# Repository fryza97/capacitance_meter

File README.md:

# capacitance_meter
A laboratory circuit for C measurements based on a direct sensor-to-microcontroller interface circuit and a PIC16F1789 microcontroller.
Engineering thesis from 2020.

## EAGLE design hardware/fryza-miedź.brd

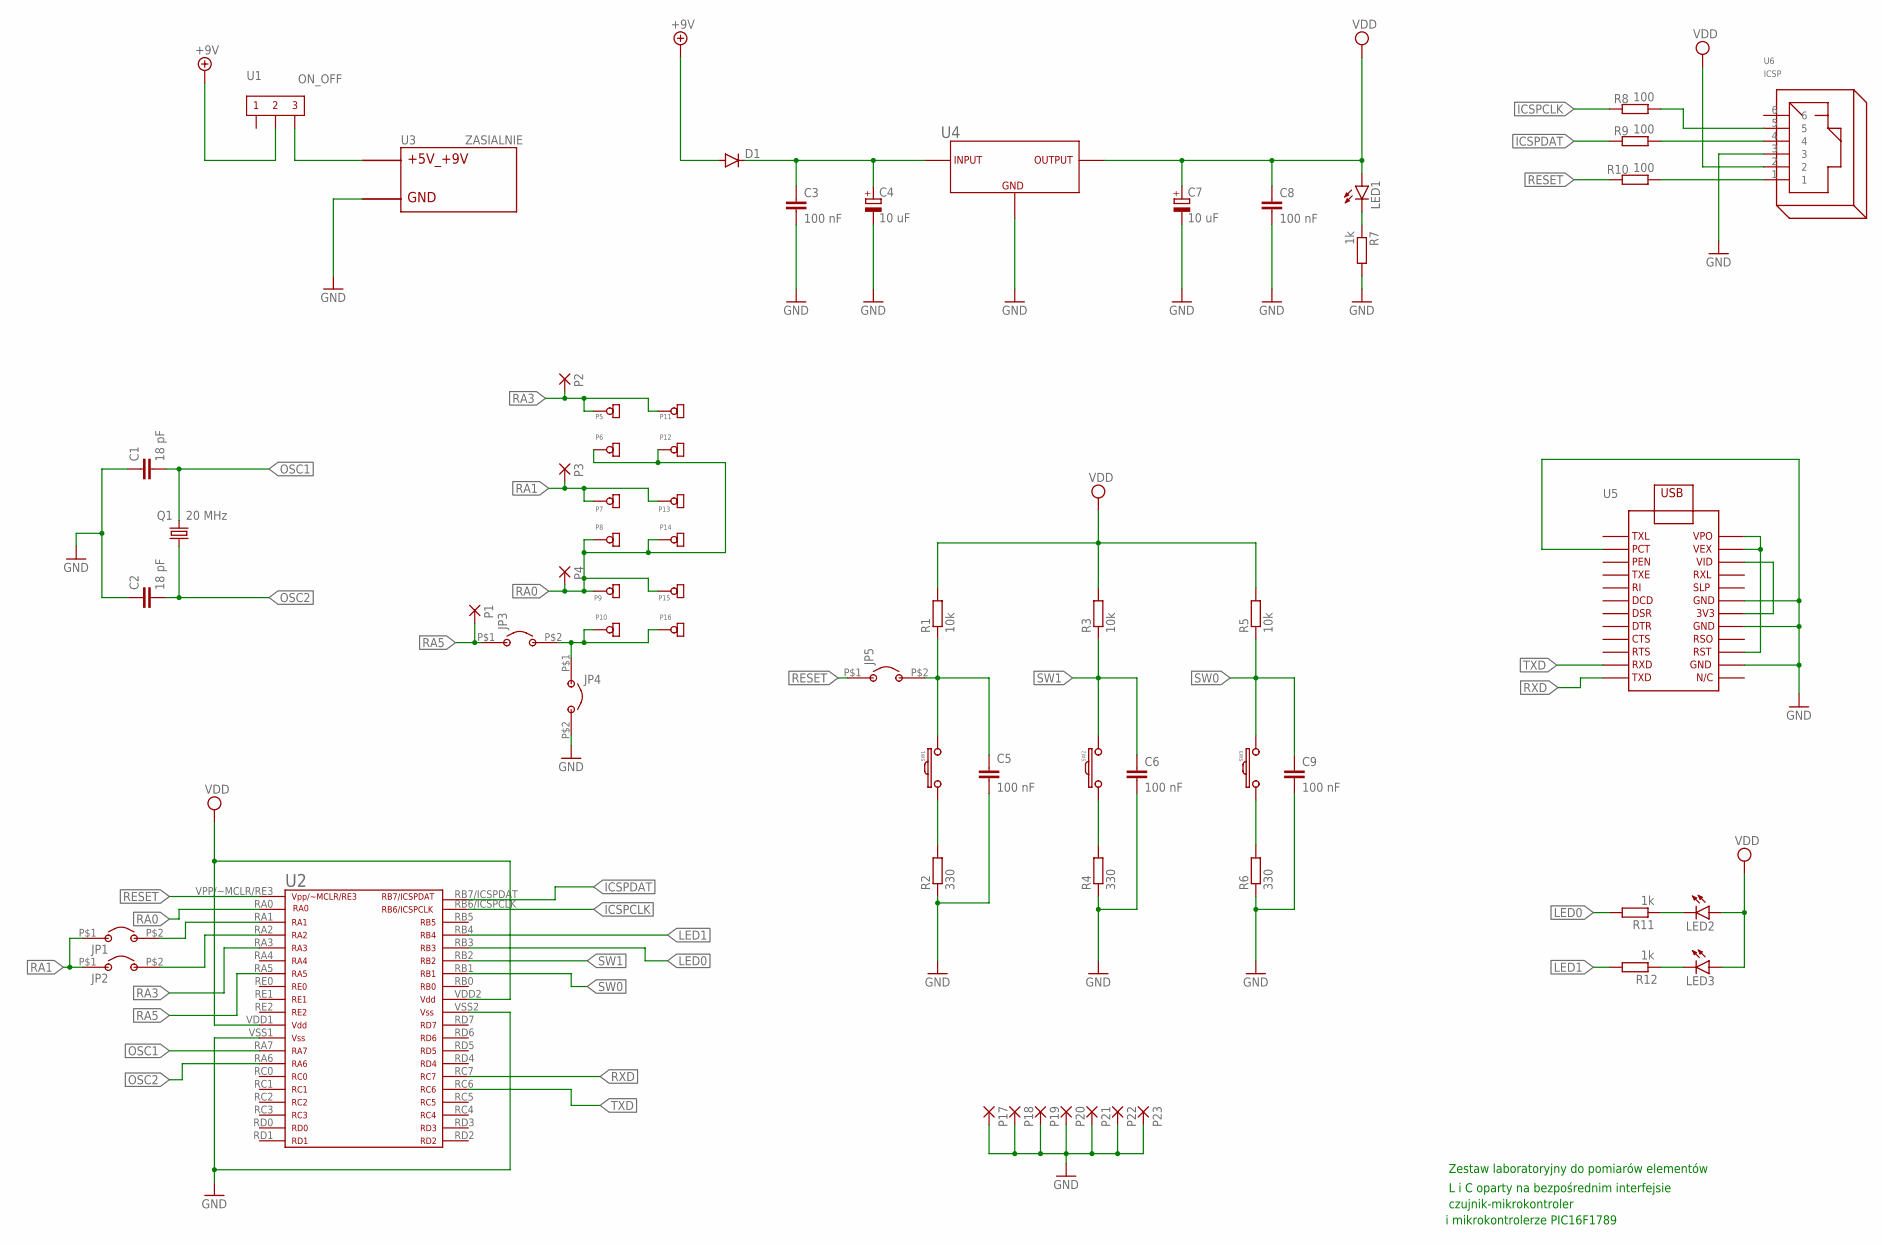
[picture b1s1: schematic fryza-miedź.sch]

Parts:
C1, C2: 18 pF; C050-035X075
C3, C5, C6, C8, C9: 100 nF; C050-035X075
C4, C7: 10 uF; E2,5-5
D1: 1N4004; DO41-10
JP1, JP2, JP3, JP4, JP5: JUMPER
LED1, LED2, LED3: LED5MM
P1, P2, P3, P4, P17, P18, P19, P20, P21, P22, P23: SZPILKA; CON
P5, P6, P7, P8, P9, P10, P11, P12, P13, P14, P15, P16: CON
Q1: 20 MHz; KWARC
R1, R3, R5: 10k; 0207/10
R2, R4, R6: 330; 0207/10
R7, R11, R12: 1k; 0207/10
R8, R9, R10: 100; 0207/10
SW1, SW2, SW3: PUSH_SWITCH
U1: ON_OFF; WLACZNIK
U2: PIC16F1789
U3: ZASIALNIE; ZASILANIE_ZLACZE
U4: LF33CV
U5: MMUSB232
U6: ICSP; RJ12

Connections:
+9V: D1.A, U1.2
GND: C1.1, C2.1, C3.2, C4.-, C5.2, C6.2, C7.-, C8.2, C9.2, JP4.P$2, P17.P$1, P18.P$1, P19.P$1, P20.P$1, P21.P$1, P22.P$1, P23.P$1, R2.1, R4.1, R6.1, R7.2, U2.VSS1, U2.VSS2, U3.GND1 (GND), U3.GND2 (GND), U4.GND, U5.GND, U5.GND1, U5.GND2, U5.PCT, U6.3
ICSPCLK: R8.2, U2.RB6/ICSPCLK
ICSPDAT: R9.2, U2.RB7/ICSPDAT
LED0: R11.2, U2.RB3
LED1: R12.2, U2.RB4
unnamed: C3.1, C4.+, D1.C, U4.INPUT
unnamed: LED1.K (C), R7.1
unnamed: U1.3, U3.V_S (+5V_+9V)
unnamed: C5.1, JP5.P$2, R1.1, SW1.1_1, SW1.1_2
unnamed: U5.RST, U5.VEX, U5.VPO
unnamed: JP3.P$2, JP4.P$1, P10.P$1, P16.P$1
unnamed: LED2.K (C), R11.1
unnamed: JP1.P$2, U2.RA1
unnamed: LED3.K (C), R12.1
unnamed: R10.1, U6.1
unnamed: R2.2, SW1.2_1, SW1.2_2
unnamed: R6.2, SW3.2_1, SW3.2_2
unnamed: R4.2, SW2.2_1, SW2.2_2
unnamed: U5.3V3, U5.VIO (VID)
unnamed: R8.1, U6.5
unnamed: R9.1, U6.4
OSC1: C1.2, Q1.P$2 (2), U2.RA7
OSC2: C2.2, Q1.P$1 (1), U2.RA6
RA0: P4.P$1, P6.P$1, P8.P$1, P9.P$1, P12.P$1, P14.P$1, P15.P$1, U2.RA0
RA1: JP1.P$1, JP2.P$1, P3.P$1, P7.P$1, P13.P$1
RA2: JP2.P$2, U2.RA2
RA3: P2.P$1, P5.P$1, P11.P$1, U2.RA3
RA5: JP3.P$1, P1.P$1, U2.RA5
RESET: JP5.P$1, R10.2, U2.VPP/~MCLR/RE3
RXD: U2.RC7, U5.TXD
SW0: C9.1, R5.1, SW3.1_1, SW3.1_2, U2.RB1
SW1: C6.1, R3.1, SW2.1_1, SW2.1_2, U2.RB2
TXD: U2.RC6, U5.RXD
VDD: C7.+, C8.1, LED1.A, LED2.A, LED3.A, R1.2, R3.2, R5.2, U2.VDD1, U2.VDD2, U4.OUTPUT, U6.2

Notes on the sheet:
Zestaw laboratoryjny do pomiarów elementów
L i C oparty na bezpośrednim interfejsie
czujnik-mikrokontroler
i mikrokontrolerze PIC16F1789

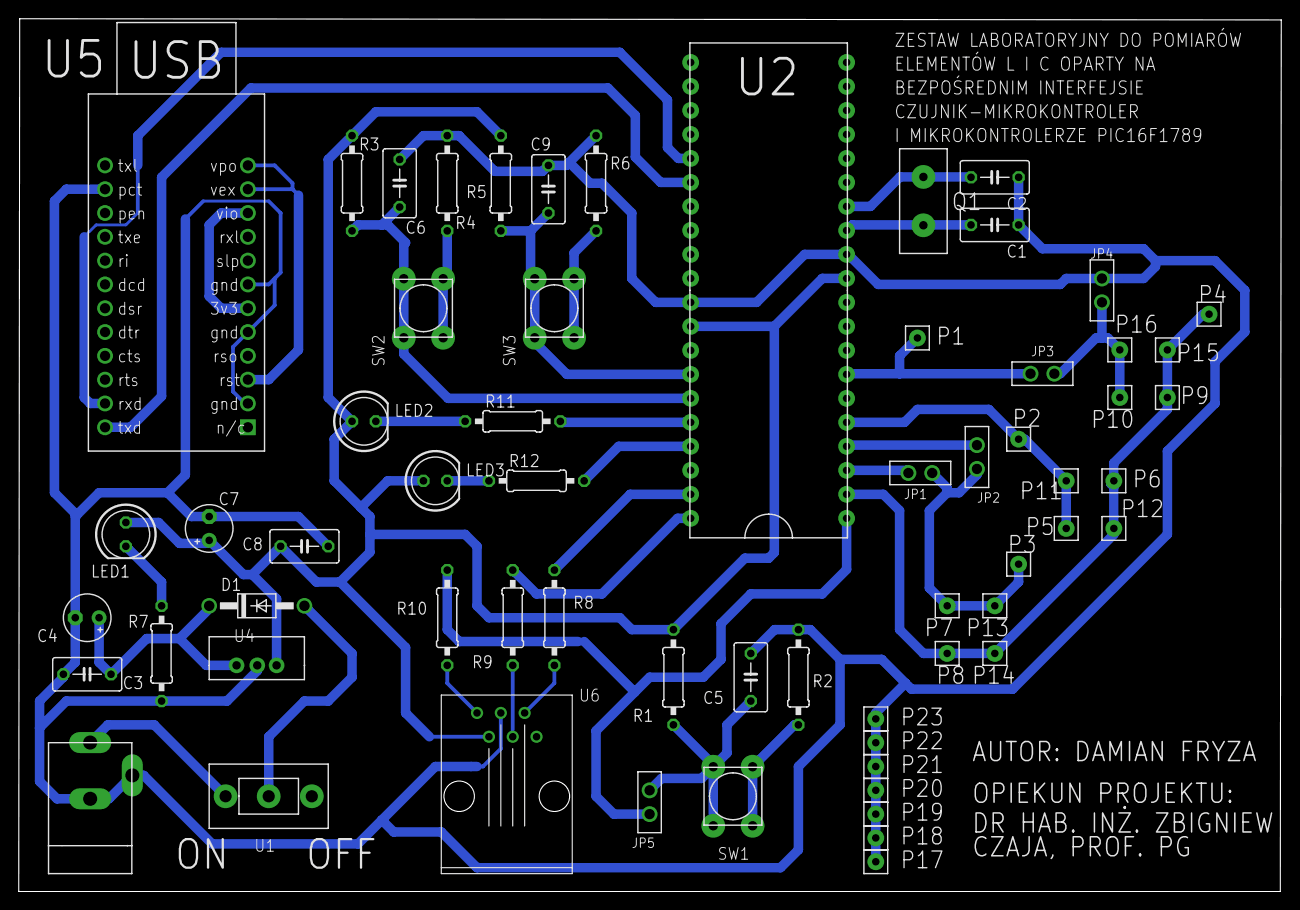
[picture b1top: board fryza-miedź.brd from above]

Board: 2 copper layers, 134.7 x 93.1 mm, 63 parts (0 on the bottom side), 35 nets.

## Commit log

2024-04-22 Add files from engineering thesis
2024-04-22 Removing unnesesery files
